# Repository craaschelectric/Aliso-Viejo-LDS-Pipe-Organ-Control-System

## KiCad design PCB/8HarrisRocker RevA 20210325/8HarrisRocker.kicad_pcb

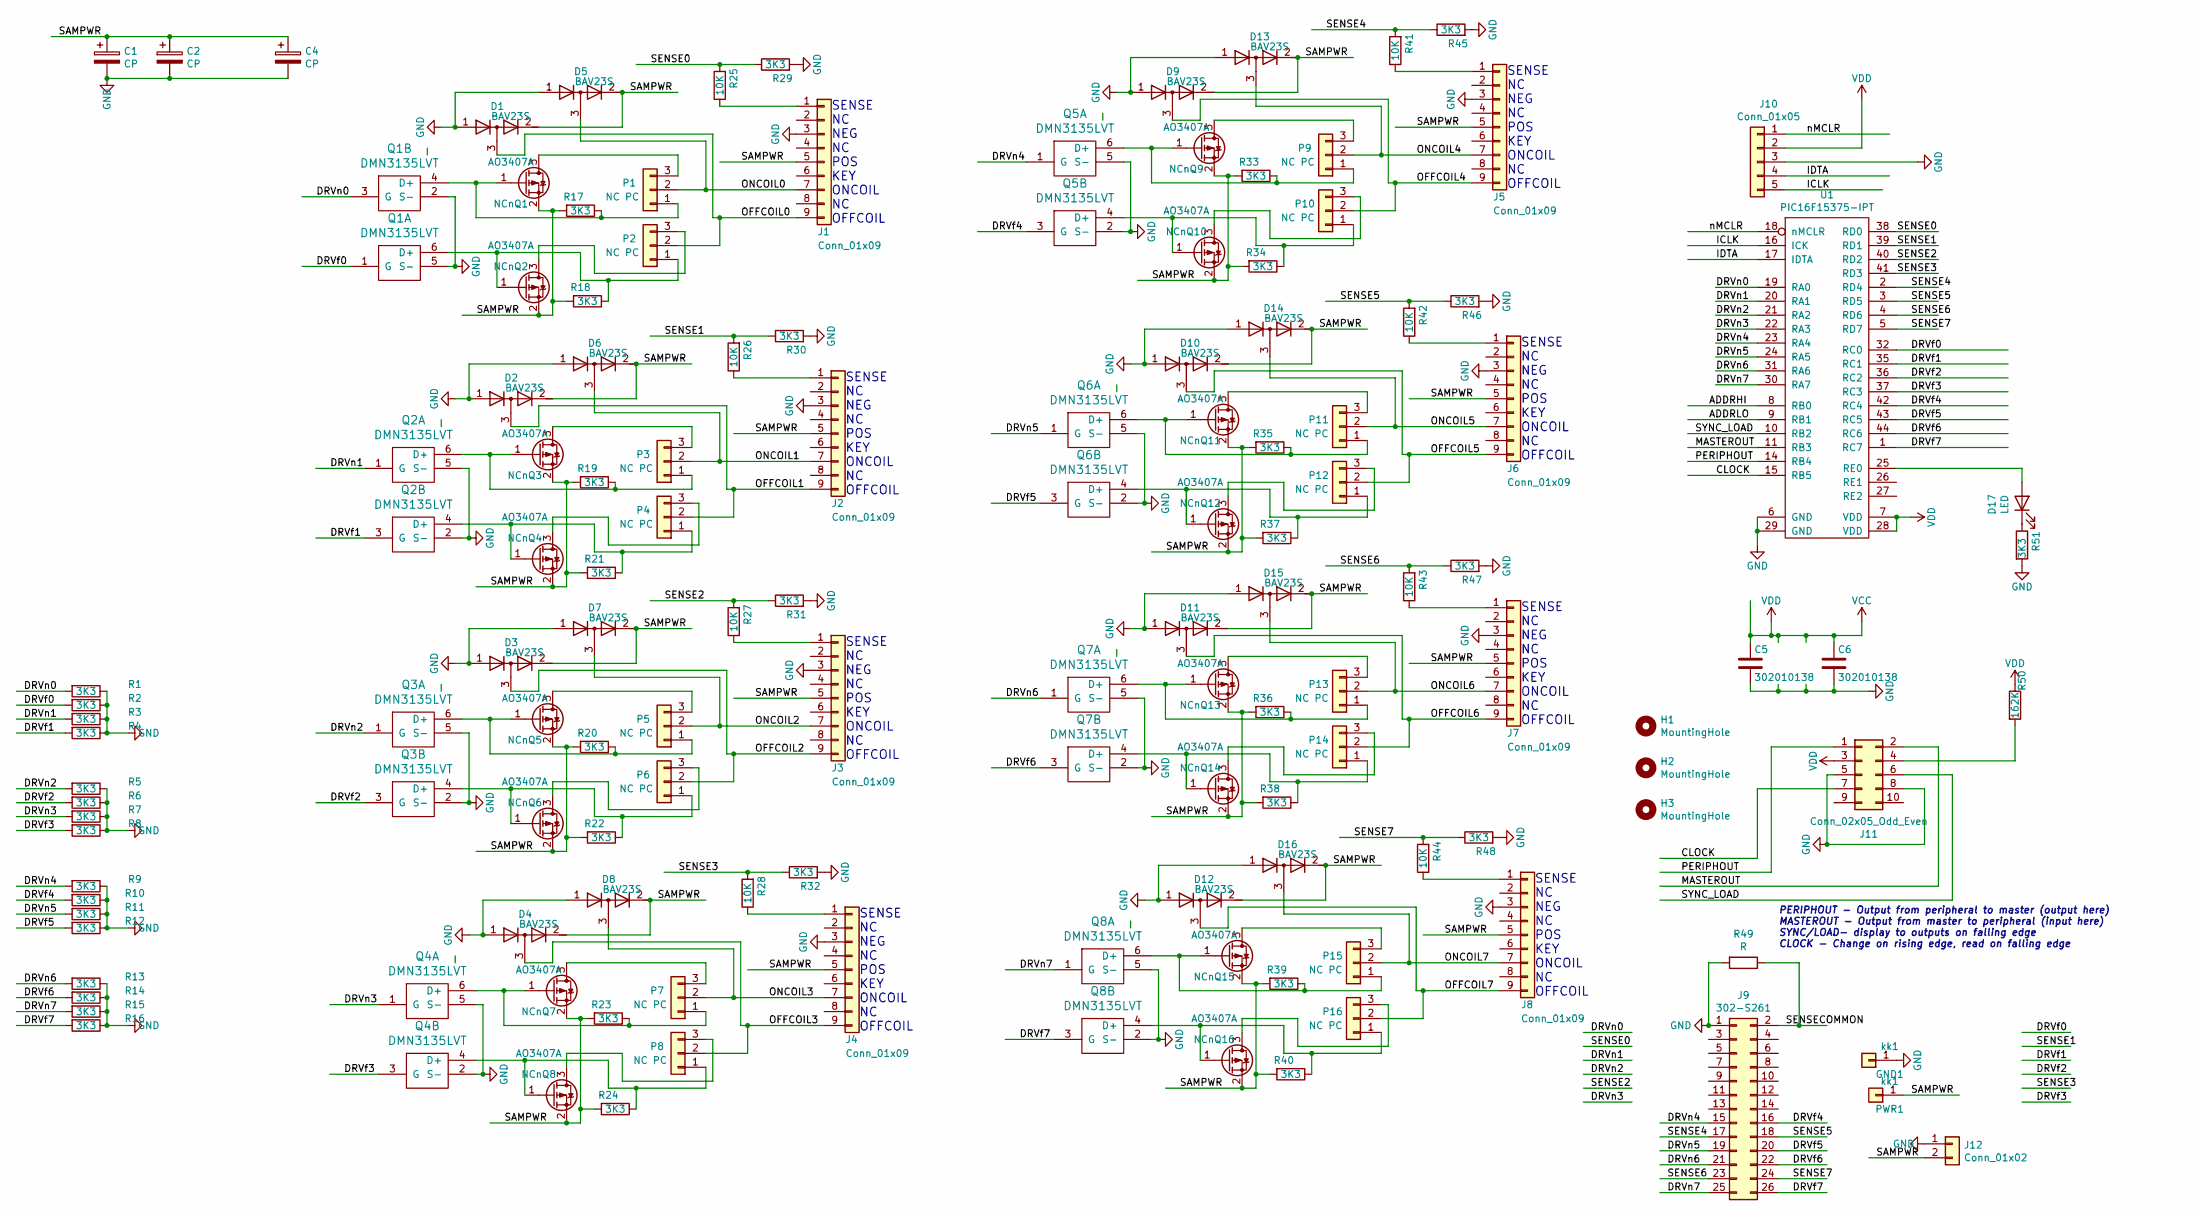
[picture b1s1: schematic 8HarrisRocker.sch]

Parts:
C1, C2, C4: CP; CP_Radial_D10.0mm_P2.50mm_P5.00mm
C5: 302010138; C_0805_2012Metric_Pad1.18x1.45mm_HandSolder
C6: 302010138; C_0603_1608Metric_Pad1.08x0.95mm_HandSolder
D1, D2, D3, D4, D5, D6, D7, D8, D9, D10, D11, D12, D13, D14, D15, D16: BAV23S; SOT-23_Handsoldering
D17: LED; LED_0805_2012Metric_Pad1.15x1.40mm_HandSolder
GND1: kk1; KK156-1
H1, H2, H3: MountingHole; MountingHole_3.2mm_M3
J1, J2, J3, J4, J5, J6, J7, J8: Conn_01x09; PinSocket_1x09_P2.54mm_Vertical
J9: 302-S261; 2x13_2.54mmShrouded
J10: Conn_01x05; PinHeader_1x05_P2.54mm_Vertical
J11: Conn_02x05_Odd_Even; RibbonCableSocket_10_OddEven
J12: Conn_01x02; TerminalBlock_Phoenix_PT-1,5-2-3.5-H_1x02_P3.50mm_Horizontal
NCnQ1, NCnQ2, NCnQ3, NCnQ4, NCnQ5, NCnQ6, NCnQ7, NCnQ8, NCnQ9, NCnQ10, NCnQ11, NCnQ12, NCnQ13, NCnQ14, NCnQ15, NCnQ16: AO3407A; SOT-23_Handsoldering
P1, P2, P3, P4, P5, P6, P7, P8, P9, P10, P11, P12, P13, P14, P15, P16: NC PC; 0603Jumper
PWR1: kk1; KK156-1
Q1, Q2, Q3, Q4, Q5, Q6, Q7, Q8: DMN3135LVT; SOT-23-6_Handsoldering
R1, R2, R3, R4, R5, R6, R7, R8, R9, R10, R11, R12, R13, R14, R15, R16, R17, R18, R19, R20, R21, R22, R23, R24, R29, R30, R31, R32, R33, R34, R35, R36, R37, R38, R39, R40, R45, R46, R47, R48, R51: 3K3; R_0603_1608Metric_Pad0.98x0.95mm_HandSolder
R25, R26, R27, R28, R41, R42, R43, R44: 10K; R_0603_1608Metric_Pad0.98x0.95mm_HandSolder
R49: R; R_0603_1608Metric_Pad0.98x0.95mm_HandSolder
R50: 162K; R_0603_1608Metric_Pad0.98x0.95mm_HandSolder
U1: PIC16F15375-IPT; LQFP-44_10x10mm_P0.8mm

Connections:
/CLOCK: J11.7, U1.15 (RB5)
/DRVf0: Q1.1 (G), R2.2, U1.32 (RC0)
/DRVf1: Q2.3 (G), R4.2, U1.35 (RC1)
/DRVf2: Q3.3 (G), R6.2, U1.36 (RC2)
/DRVf3: Q4.3 (G), R8.2, U1.37 (RC3)
/DRVf4: J9.16, Q5.3 (G), R10.2, U1.42 (RC4)
/DRVf5: J9.20, Q6.3 (G), R12.2, U1.43 (RC5)
/DRVf6: J9.22, Q7.3 (G), R14.2, U1.44 (RC6)
/DRVf7: J9.26, Q8.3 (G), R16.2, U1.1 (RC7)
/DRVn0: Q1.3 (G), R1.2, U1.19 (RA0)
/DRVn1: Q2.1 (G), R3.2, U1.20 (RA1)
/DRVn2: Q3.1 (G), R5.2, U1.21 (RA2)
/DRVn3: Q4.1 (G), R7.2, U1.22 (RA3)
/DRVn4: J9.15, Q5.1 (G), R9.2, U1.23 (RA4)
/DRVn5: J9.19, Q6.1 (G), R11.2, U1.24 (RA5)
/DRVn6: J9.21, Q7.1 (G), R13.2, U1.31 (RA6)
/DRVn7: J9.25, Q8.1 (G), R15.2, U1.30 (RA7)
/ICLK: J10.5, U1.16 (ICK)
/IDTA: J10.4, U1.17 (IDTA)
/MASTEROUT: J11.2, U1.11 (RB3)
/OFFCOIL0: D1.3 (common), J1.9, P2.2
/OFFCOIL1: D2.3 (common), J2.9, P4.2
/OFFCOIL2: D3.3 (common), J3.9, P6.2
/OFFCOIL3: D4.3 (common), J4.9, P8.2
/OFFCOIL4: D9.3 (common), J5.9, P10.2
/OFFCOIL5: D10.3 (common), J6.9, P12.2
/OFFCOIL6: D11.3 (common), J7.9, P14.2
/OFFCOIL7: D12.3 (common), J8.9, P16.2
/ONCOIL0: D5.3 (common), J1.7, P1.2
/ONCOIL1: D6.3 (common), J2.7, P3.2
/ONCOIL2: D7.3 (common), J3.7, P5.2
/ONCOIL3: D8.3 (common), J4.7, P7.2
/ONCOIL4: D13.3 (common), J5.7, P9.2
/ONCOIL5: D14.3 (common), J6.7, P11.2
/ONCOIL6: D15.3 (common), J7.7, P13.2
/ONCOIL7: D16.3 (common), J8.7, P15.2
/PERIPHOUT: J11.1, U1.14 (RB4)
/SAMPWR: C1.1, C2.1, C4.1, D1.2 (K), D2.2 (K), D3.2 (K), D4.2 (K), D5.2 (K), D6.2 (K), D7.2 (K), D8.2 (K), D9.2 (K), D10.2 (K), D11.2 (K), D12.2 (K), D13.2 (K), D14.2 (K), D15.2 (K), D16.2 (K), J1.5, J2.5, J3.5, J4.5, J5.5, J6.5, J7.5, J8.5, J12.2, NCnQ1.2 (S), NCnQ2.2 (S), NCnQ3.2 (S), NCnQ4.2 (S), NCnQ5.2 (S), NCnQ6.2 (S), NCnQ7.2 (S), NCnQ8.2 (S), NCnQ9.2 (S), NCnQ10.2 (S), NCnQ11.2 (S), NCnQ12.2 (S), NCnQ13.2 (S), NCnQ14.2 (S), NCnQ15.2 (S), NCnQ16.2 (S), PWR1.1, R17.2, R18.2, R19.2, R20.2, R21.2, R22.2, R23.2, R24.2, R33.2, R34.2, R35.2, R36.2, R37.2, R38.2, R39.2, R40.2
/SENSE0: R25.2, R29.1, U1.38 (RD0)
/SENSE1: R26.2, R30.1, U1.39 (RD1)
/SENSE2: R27.2, R31.1, U1.40 (RD2)
/SENSE3: R28.2, R32.1, U1.41 (RD3)
/SENSE4: J9.17, R41.2, R45.1, U1.2 (RD4)
/SENSE5: J9.18, R42.2, R46.1, U1.3 (RD5)
/SENSE6: J9.23, R43.2, R47.1, U1.4 (RD6)
/SENSE7: J9.24, R44.2, R48.1, U1.5 (RD7)
/SENSECOMMON: J9.2, R49.1
/SYNC_LOAD: J11.6, U1.10 (RB2)
/nMCLR: J10.1, U1.18 (nMCLR)
GND: C1.2, C2.2, C4.2, C5.2, C6.2, D1.1 (A), D2.1 (A), D3.1 (A), D4.1 (A), D5.1 (A), D6.1 (A), D7.1 (A), D8.1 (A), D9.1 (A), D10.1 (A), D11.1 (A), D12.1 (A), D13.1 (A), D14.1 (A), D15.1 (A), D16.1 (A), GND1.1, J1.3, J2.3, J3.3, J4.3, J5.3, J6.3, J7.3, J8.3, J9.1, J10.3, J11.5, J11.8, J12.1, Q1.2 (S-), Q1.5 (S-), Q2.2 (S-), Q2.5 (S-), Q3.2 (S-), Q3.5 (S-), Q4.2 (S-), Q4.5 (S-), Q5.2 (S-), Q5.5 (S-), Q6.2 (S-), Q6.5 (S-), Q7.2 (S-), Q7.5 (S-), Q8.2 (S-), Q8.5 (S-), R1.1, R2.1, R3.1, R4.1, R5.1, R6.1, R7.1, R8.1, R9.1, R10.1, R11.1, R12.1, R13.1, R14.1, R15.1, R16.1, R29.2, R30.2, R31.2, R32.2, R45.2, R46.2, R47.2, R48.2, R49.2, R51.2, U1.6 (GND), U1.29 (GND)
unnamed: D17.1 (K), R51.1
unnamed: D17.2 (A), U1.25 (RE0)
unnamed: J1.1, R25.1
unnamed: J2.1, R26.1
unnamed: J3.1, R27.1
unnamed: J4.1, R28.1
unnamed: J5.1, R41.1
unnamed: J6.1, R42.1
unnamed: J7.1, R43.1
unnamed: J8.1, R44.1
unnamed: J11.4, R50.2
unnamed: NCnQ1.1 (G), P1.1, Q1.4 (D+), R17.1
unnamed: NCnQ1.3 (D), P1.3
unnamed: NCnQ2.1 (G), P2.1, Q1.6 (D+), R18.1
unnamed: NCnQ2.3 (D), P2.3
unnamed: NCnQ3.1 (G), P3.1, Q2.6 (D+), R19.1
unnamed: NCnQ3.3 (D), P3.3
unnamed: NCnQ4.1 (G), P4.1, Q2.4 (D+), R21.1
unnamed: NCnQ4.3 (D), P4.3
unnamed: NCnQ5.1 (G), P5.1, Q3.6 (D+), R20.1
unnamed: NCnQ5.3 (D), P5.3
unnamed: NCnQ6.1 (G), P6.1, Q3.4 (D+), R22.1
unnamed: NCnQ6.3 (D), P6.3
unnamed: NCnQ7.1 (G), P7.1, Q4.6 (D+), R23.1
unnamed: NCnQ7.3 (D), P7.3
unnamed: NCnQ8.1 (G), P8.1, Q4.4 (D+), R24.1
unnamed: NCnQ8.3 (D), P8.3
unnamed: NCnQ9.1 (G), P9.1, Q5.6 (D+), R33.1
unnamed: NCnQ9.3 (D), P9.3
unnamed: NCnQ10.1 (G), P10.1, Q5.4 (D+), R34.1
unnamed: NCnQ10.3 (D), P10.3
unnamed: NCnQ11.1 (G), P11.1, Q6.6 (D+), R35.1
unnamed: NCnQ11.3 (D), P11.3
unnamed: NCnQ12.1 (G), P12.1, Q6.4 (D+), R37.1
unnamed: NCnQ12.3 (D), P12.3
unnamed: NCnQ13.1 (G), P13.1, Q7.6 (D+), R36.1
unnamed: NCnQ13.3 (D), P13.3
unnamed: NCnQ14.1 (G), P14.1, Q7.4 (D+), R38.1
unnamed: NCnQ14.3 (D), P14.3
unnamed: NCnQ15.1 (G), P15.1, Q8.6 (D+), R39.1
unnamed: NCnQ15.3 (D), P15.3
unnamed: NCnQ16.1 (G), P16.1, Q8.4 (D+), R40.1
unnamed: NCnQ16.3 (D), P16.3
VCC: C5.1, C6.1, J10.2, J11.3, R50.1, U1.7 (VDD), U1.28 (VDD)

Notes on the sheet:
SENSE NC NEG NC POS KEY ONCOIL NC OFFCOIL
PERIPHOUT - Output from peripheral to master (output here) MASTEROUT - Output from master to peripheral (input here) SYNC/LOAD- display to outputs on falling edge CLOCK - Change on rising edge, read on falling edge

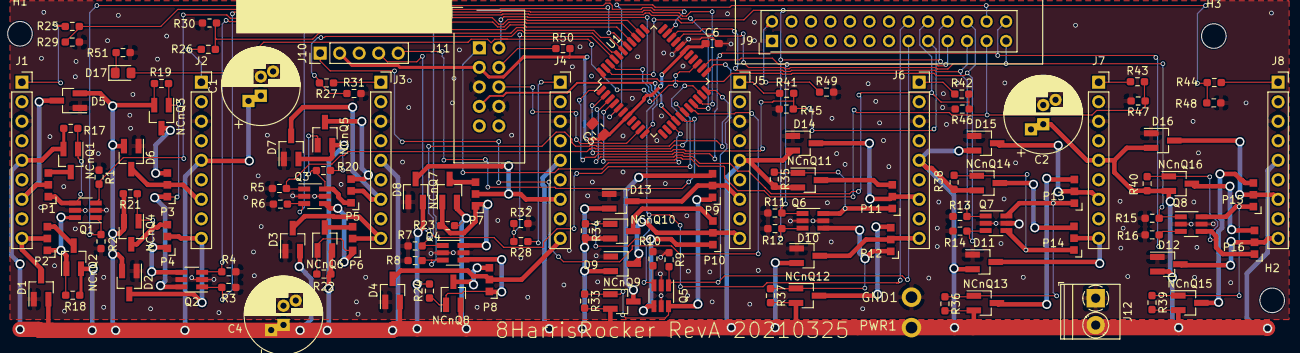
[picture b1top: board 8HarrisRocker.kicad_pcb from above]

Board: 2 copper layers, 131 parts (0 on the bottom side), 94 nets.

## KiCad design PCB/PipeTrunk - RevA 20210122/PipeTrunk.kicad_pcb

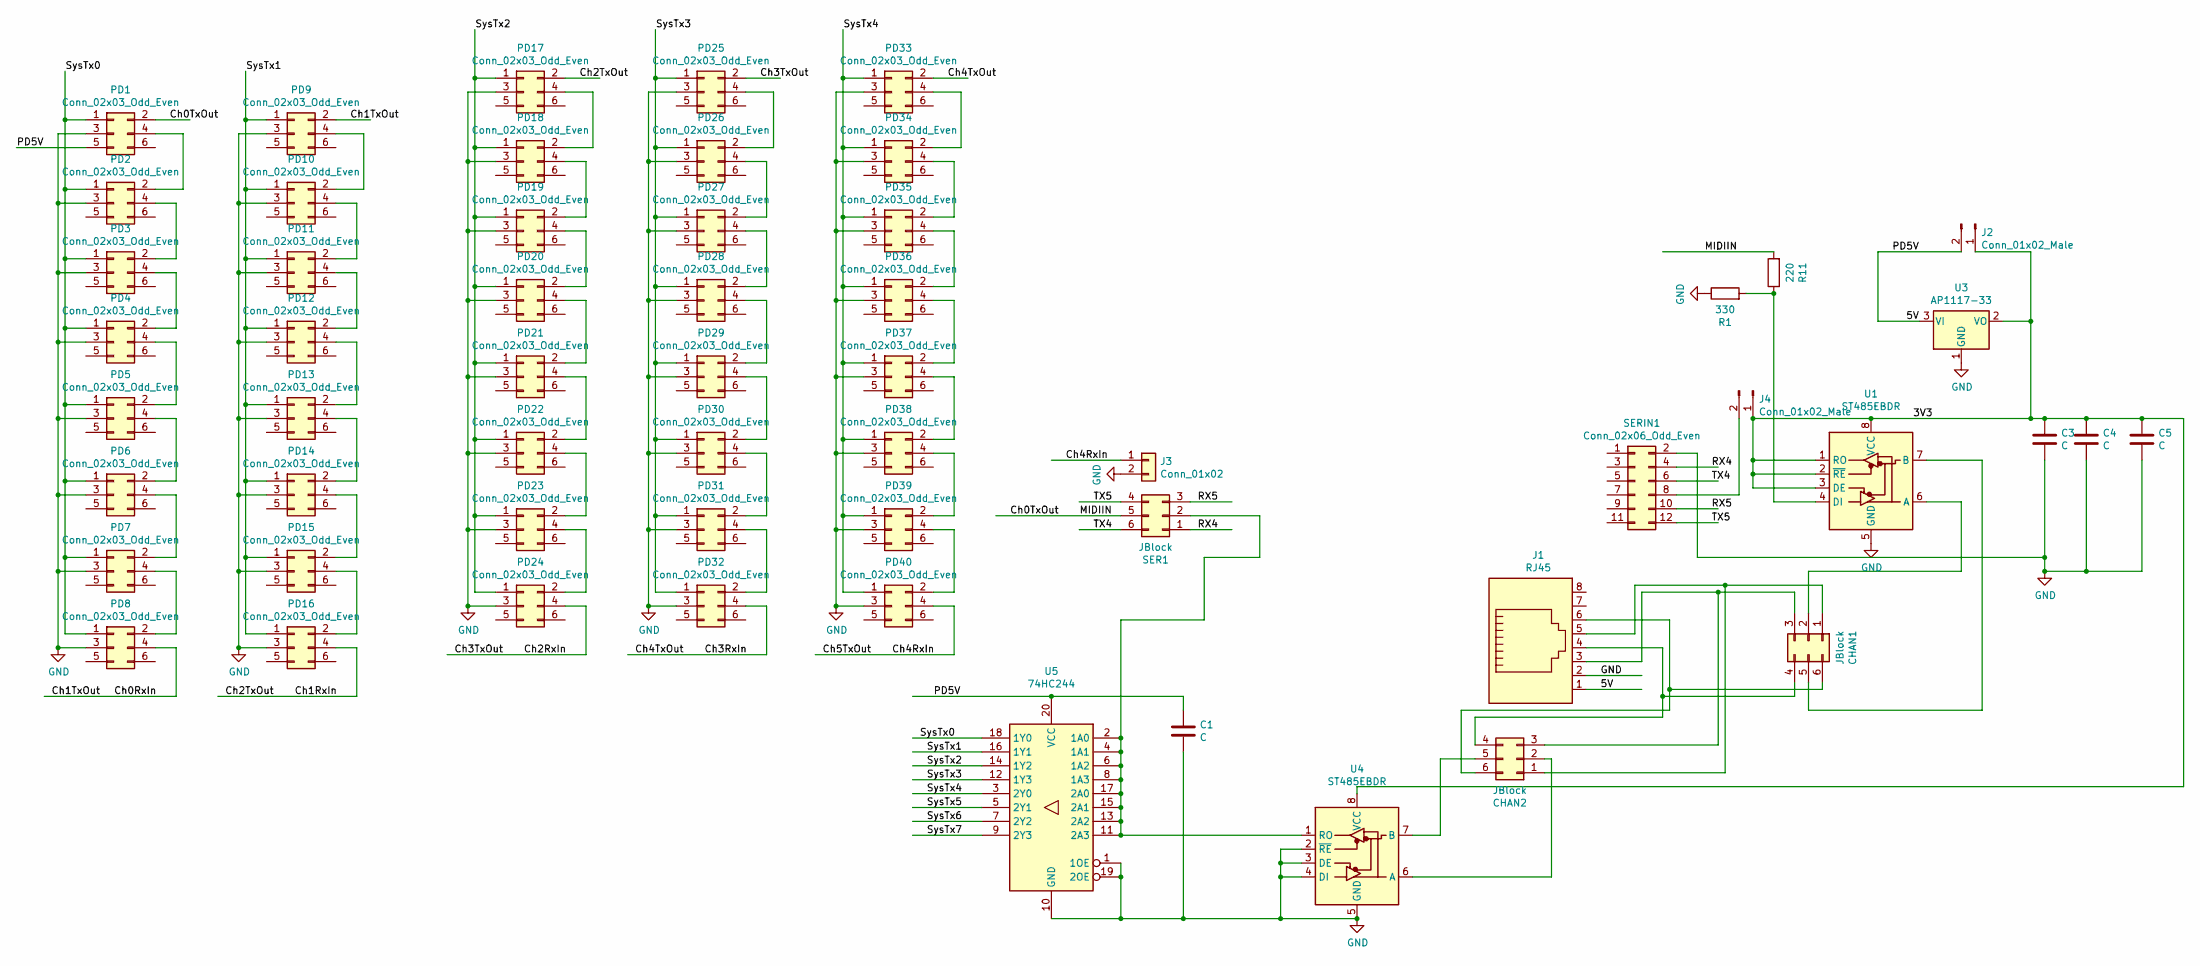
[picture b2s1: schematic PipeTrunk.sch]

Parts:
C1, C3: C; C_0603_1608Metric_Pad1.08x0.95mm_HandSolder
C4, C5: C; C_0805_2012Metric_Pad1.15x1.40mm_HandSolder
CHAN1, CHAN2: JBlock; H2X3-2.54
J1: RJ45; RJ45_Amphenol_54602-x08_Horizontal
J2, J4: Conn_01x02_Male; H2-2.54
J3: Conn_01x02; H2-2.54
PD1, PD2, PD3, PD4, PD5, PD6, PD7, PD8, PD9, PD10, PD11, PD12, PD13, PD14, PD15, PD16, PD17, PD18, PD19, PD20, PD21, PD22, PD23, PD24, PD25, PD26, PD27, PD28, PD29, PD30, PD31, PD32, PD33, PD34, PD35, PD36, PD37, PD38, PD39, PD40: Conn_02x03_Odd_Even; RibbonCableSocket_6_OddEven
R1: 330; R_0603_1608Metric_Pad0.98x0.95mm_HandSolder
R11: 220; R_0603_1608Metric_Pad0.98x0.95mm_HandSolder
SER1: JBlock; H2X3-2.54
SERIN1: Conn_02x06_Odd_Even; RibbonCableSocket_12_OddEven
U1, U4: ST485EBDR; SOIC-8_3.9x4.9mm_P1.27mm
U3: AP1117-33; SOT-223-3_TabPin2
U5: 74HC244; SOIC-20W_7.5x12.8mm_P1.27mm

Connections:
/3V3: C3.1, C4.1, C5.1, J2.1, J4.1, U1.1 (RO), U1.2 (~RE), U1.3 (DE), U1.8 (VCC), U3.2 (VO), U4.8 (VCC)
/5V: C1.1, J1.1, J2.2, PD1.5, U3.3 (VI), U5.20 (VCC)
/Ch0RxIn: PD8.4, PD9.2
/Ch0TxOut: PD1.2, R11.2, SER1.5
/Ch1RxIn: PD16.4, PD17.2
/Ch2RxIn: PD24.4, PD25.2
/Ch3RxIn: PD32.4, PD33.2
/Ch4RxIn: J3.1, PD40.4
/RX4: SER1.1, SERIN1.4
/RX5: SER1.3, SERIN1.10
/SysTx0: PD1.1, PD2.1, PD3.1, PD4.1, PD5.1, PD6.1, PD7.1, PD8.1, U5.18 (1Y0)
/SysTx1: PD9.1, PD10.1, PD11.1, PD12.1, PD13.1, PD14.1, PD15.1, PD16.1, U5.16 (1Y1)
/SysTx2: PD17.1, PD18.1, PD19.1, PD20.1, PD21.1, PD22.1, PD23.1, PD24.1, U5.14 (1Y2)
/SysTx3: PD25.1, PD26.1, PD27.1, PD28.1, PD29.1, PD30.1, PD31.1, PD32.1, U5.12 (1Y3)
/SysTx4: PD33.1, PD34.1, PD35.1, PD36.1, PD37.1, PD38.1, PD39.1, PD40.1, U5.3 (2Y0)
/TX4: SER1.6, SERIN1.6
/TX5: SER1.4, SERIN1.12
GND: C1.2, C3.2, C4.2, C5.2, J1.2, J3.2, PD1.3, PD2.3, PD3.3, PD4.3, PD5.3, PD6.3, PD7.3, PD8.3, PD9.3, PD10.3, PD11.3, PD12.3, PD13.3, PD14.3, PD15.3, PD16.3, PD17.3, PD18.3, PD19.3, PD20.3, PD21.3, PD22.3, PD23.3, PD24.3, PD25.3, PD26.3, PD27.3, PD28.3, PD29.3, PD30.3, PD31.3, PD32.3, PD33.3, PD34.3, PD35.3, PD36.3, PD37.3, PD38.3, PD39.3, PD40.3, R1.1, SERIN1.2, U1.5 (GND), U3.1 (GND), U4.2 (~RE), U4.3 (DE), U4.4 (DI), U4.5 (GND), U5.1 (1OE), U5.10 (GND), U5.19 (2OE)
unnamed: CHAN1.1, CHAN2.1, J1.5
unnamed: CHAN1.2, U1.6 (A)
unnamed: CHAN1.3, CHAN2.3, J1.3
unnamed: CHAN1.4, CHAN2.4, J1.4
unnamed: CHAN1.5, U1.7 (B)
unnamed: CHAN1.6, CHAN2.6, J1.6
unnamed: CHAN2.2, U4.6 (A)
unnamed: CHAN2.5, U4.7 (B)
unnamed: J4.2, SERIN1.8
unnamed: PD1.4, PD2.2
unnamed: PD2.4, PD3.2
unnamed: PD3.4, PD4.2
unnamed: PD4.4, PD5.2
unnamed: PD5.4, PD6.2
unnamed: PD6.4, PD7.2
unnamed: PD7.4, PD8.2
unnamed: PD9.4, PD10.2
unnamed: PD10.4, PD11.2
unnamed: PD11.4, PD12.2
unnamed: PD12.4, PD13.2
unnamed: PD13.4, PD14.2
unnamed: PD14.4, PD15.2
unnamed: PD15.4, PD16.2
unnamed: PD17.4, PD18.2
unnamed: PD18.4, PD19.2
unnamed: PD19.4, PD20.2
unnamed: PD20.4, PD21.2
unnamed: PD21.4, PD22.2
unnamed: PD22.4, PD23.2
unnamed: PD23.4, PD24.2
unnamed: PD25.4, PD26.2
unnamed: PD26.4, PD27.2
unnamed: PD27.4, PD28.2
unnamed: PD28.4, PD29.2
unnamed: PD29.4, PD30.2
unnamed: PD30.4, PD31.2
unnamed: PD31.4, PD32.2
unnamed: PD33.4, PD34.2
unnamed: PD34.4, PD35.2
unnamed: PD35.4, PD36.2
unnamed: PD36.4, PD37.2
unnamed: PD37.4, PD38.2
unnamed: PD38.4, PD39.2
unnamed: PD39.4, PD40.2
unnamed: R1.2, R11.1, U1.4 (DI)
unnamed: SER1.2, U4.1 (RO), U5.2 (1A0), U5.4 (1A1), U5.6 (1A2), U5.8 (1A3), U5.11 (2A3), U5.13 (2A2), U5.15 (2A1), U5.17 (2A0)

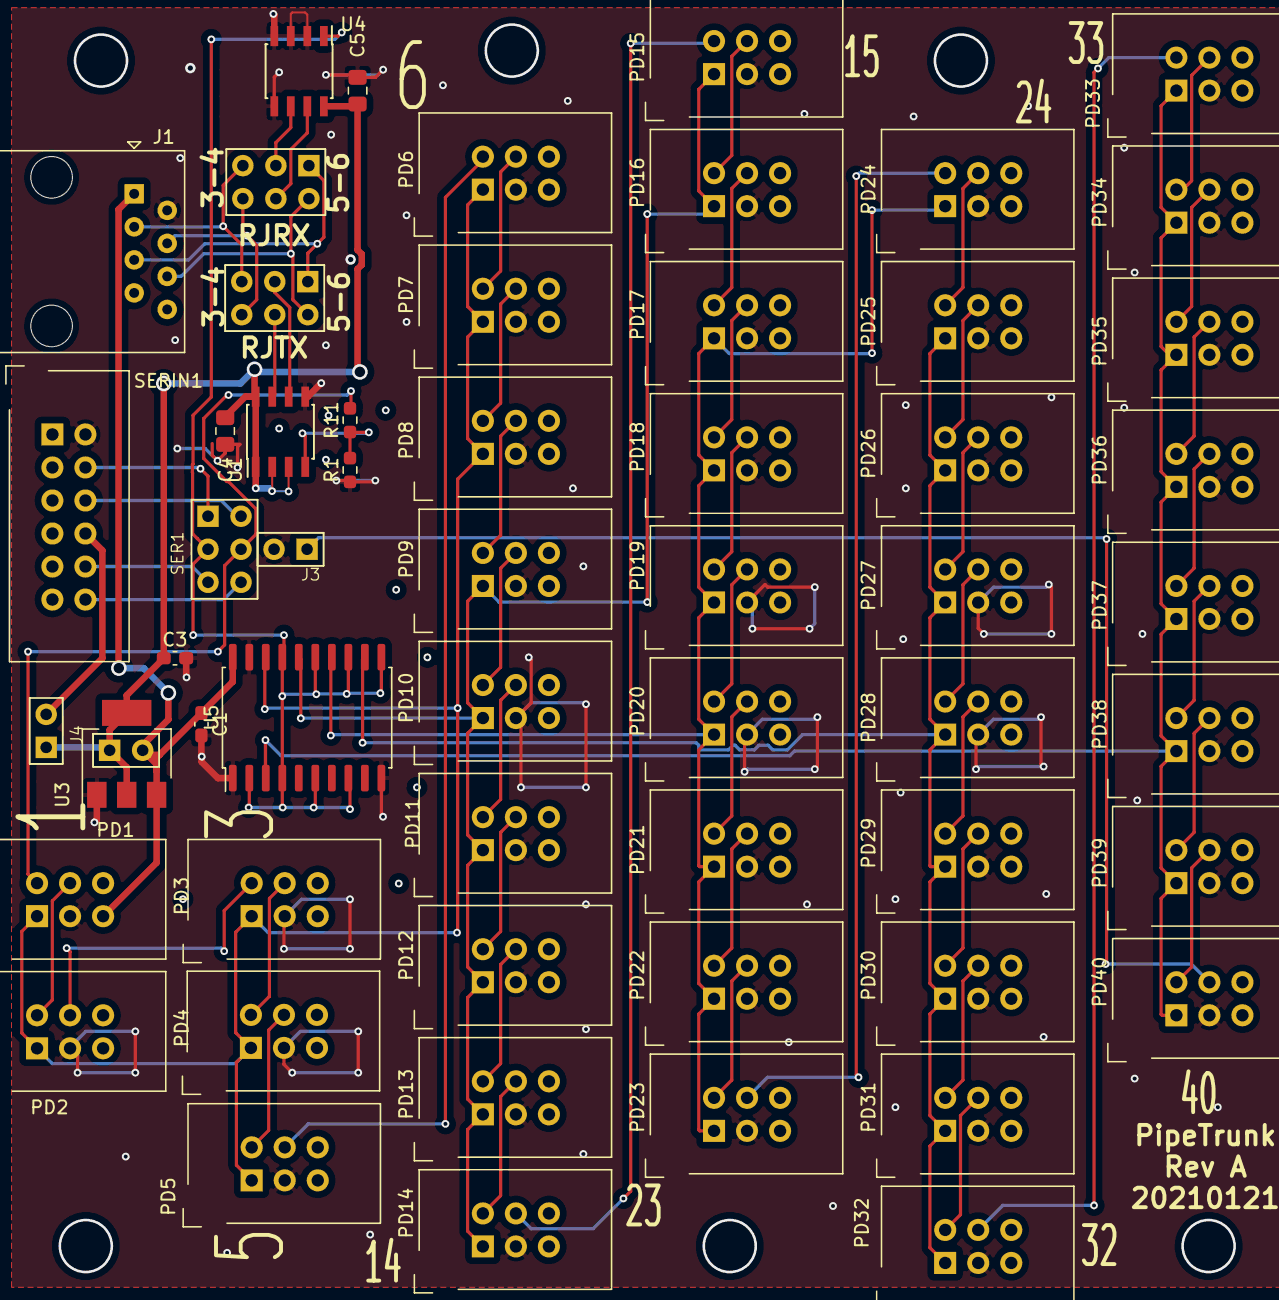
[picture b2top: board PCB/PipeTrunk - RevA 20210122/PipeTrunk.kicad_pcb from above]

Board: 2 copper layers, 58 parts (0 on the bottom side), 64 nets.

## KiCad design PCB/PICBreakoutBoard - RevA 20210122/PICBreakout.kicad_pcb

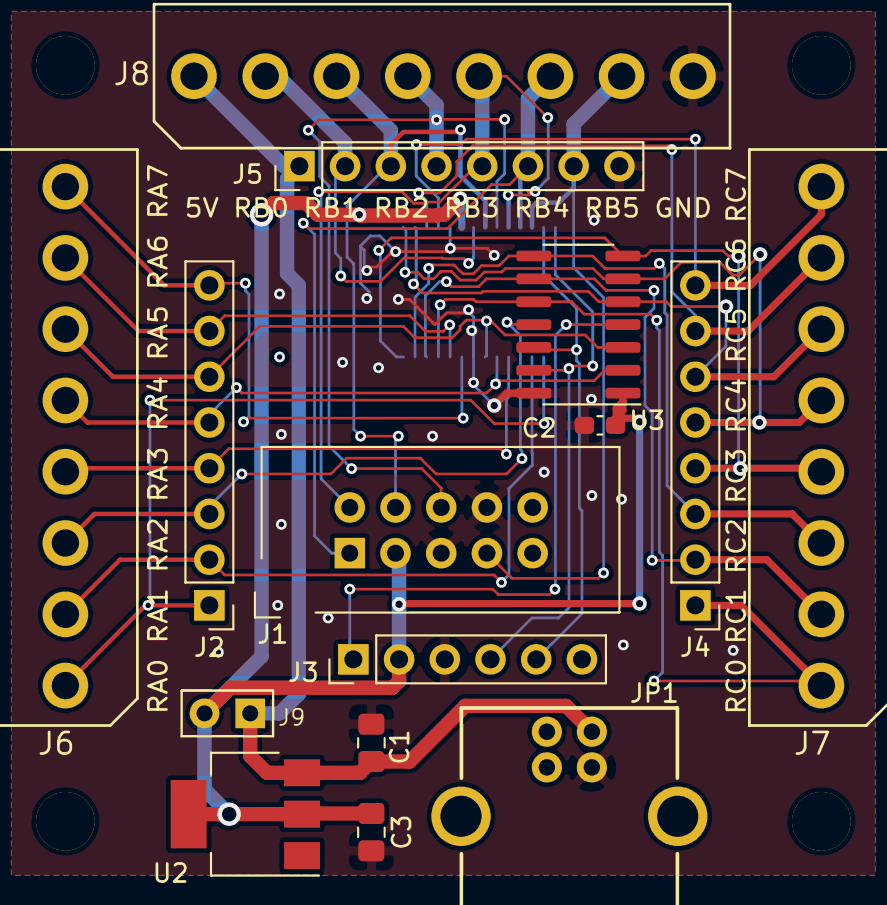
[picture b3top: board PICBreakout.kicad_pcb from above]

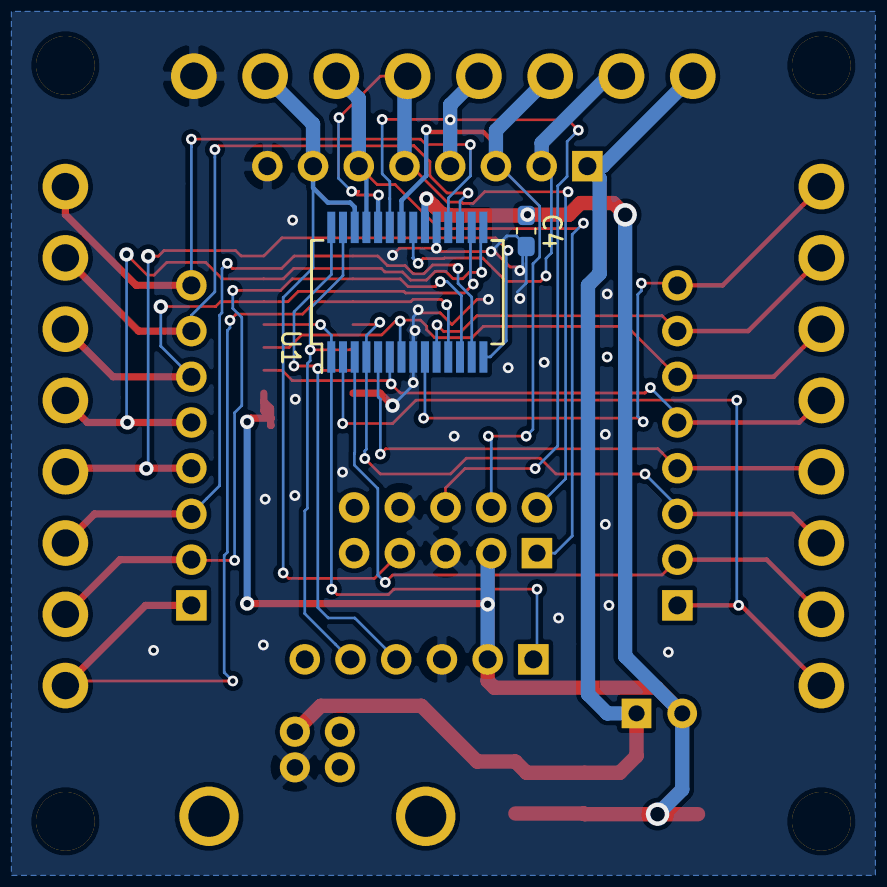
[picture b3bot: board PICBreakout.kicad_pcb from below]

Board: 2 copper layers, 21 parts (2 on the bottom side), 28 nets.

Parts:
C1, C3: 302010138; C_0805_2012Metric_Pad1.18x1.45mm_HandSolder
C2, C4: 302010138; C_0603_1608Metric_Pad1.08x0.95mm_HandSolder
J1: Conn_02x05_Odd_Even; RibbonCableSocket_10_OddEven
J2, J4, J5: Conn_01x08; PinHeader_1x08_P2.54mm_Vertical
J3: Conn_01x05; PinHeader_1x06_P2.54mm_Vertical
J6, J7, J8: Conn_01x08; KK156-8
J9: Conn_01x02; H2-2.54
JP1: DIP-USB-B-TYPE-FMAL_4+2P-2.0-90D_; USB4+2-2.5-90D-15.8X12MM
M1, M2, M3, M4: Conn_01x01; Mounting#4
U1: PIC18F26Q10-SS; SSOP-28_5.3x10.2mm_P0.65mm
U2: LM1117-3.3; SOT-223-3_TabPin2
U3: PIC16F1525; SO-14_3.9x8.65mm_P1.27mm

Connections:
/5V: C1.1, J5.1, J8.1, J9.1, JP1.VBUS, U2.3
/CLK: J1.7, J5.7, J8.7, U1.26
/MSTOUT: J1.2, J5.5, J8.5, U1.24
/PEROUT: J1.1, J5.6, J8.6, U1.25
/RA0: J2.1, J6.1, U1.2
/RA1: J2.2, J6.2, U1.3
/RA2: J2.3, J6.3, U1.4, U3.11
/RA3: J2.4, J6.4, U1.5
/RA4: J2.5, J6.5, U1.6, U3.2
/RA5: J2.6, J6.6, U1.7, U3.3
/RA6: J2.7, J6.7, U1.10
/RA7: J2.8, J6.8, U1.9
/RB0: J5.2, J8.2, U1.21
/RC0: J4.1, J7.1, U1.11, U3.10
/RC1: J4.2, J7.2, U1.12, U3.9
/RC2: J4.3, J7.3, U1.13, U3.8
/RC3: J4.4, J7.4, U1.14, U3.7
/RC4: J4.5, J7.5, U1.15, U3.6
/RC5: J4.6, J7.6, U1.16, U3.5
/RC6: J4.7, J7.7, U1.17
/RC7: J4.8, J7.8, U1.18
/SYNC: J1.6, J5.4, J8.4, U1.23
/nRST: J1.4, J5.3, J8.3, U1.22
GND: C1.2, C2.2, C3.2, C4.2, J1.5, J1.8, J3.3, J5.8, J8.8, JP1.GND, U1.8, U1.19, U3.14
unnamed: J3.1, U1.1, U3.4
unnamed: J3.4, U1.28, U3.13
unnamed: J3.5, U1.27, U3.12
VDD: C2.1, C3.1, C4.1, J1.3, J3.2, J9.2, U1.20, U2.2, U3.1

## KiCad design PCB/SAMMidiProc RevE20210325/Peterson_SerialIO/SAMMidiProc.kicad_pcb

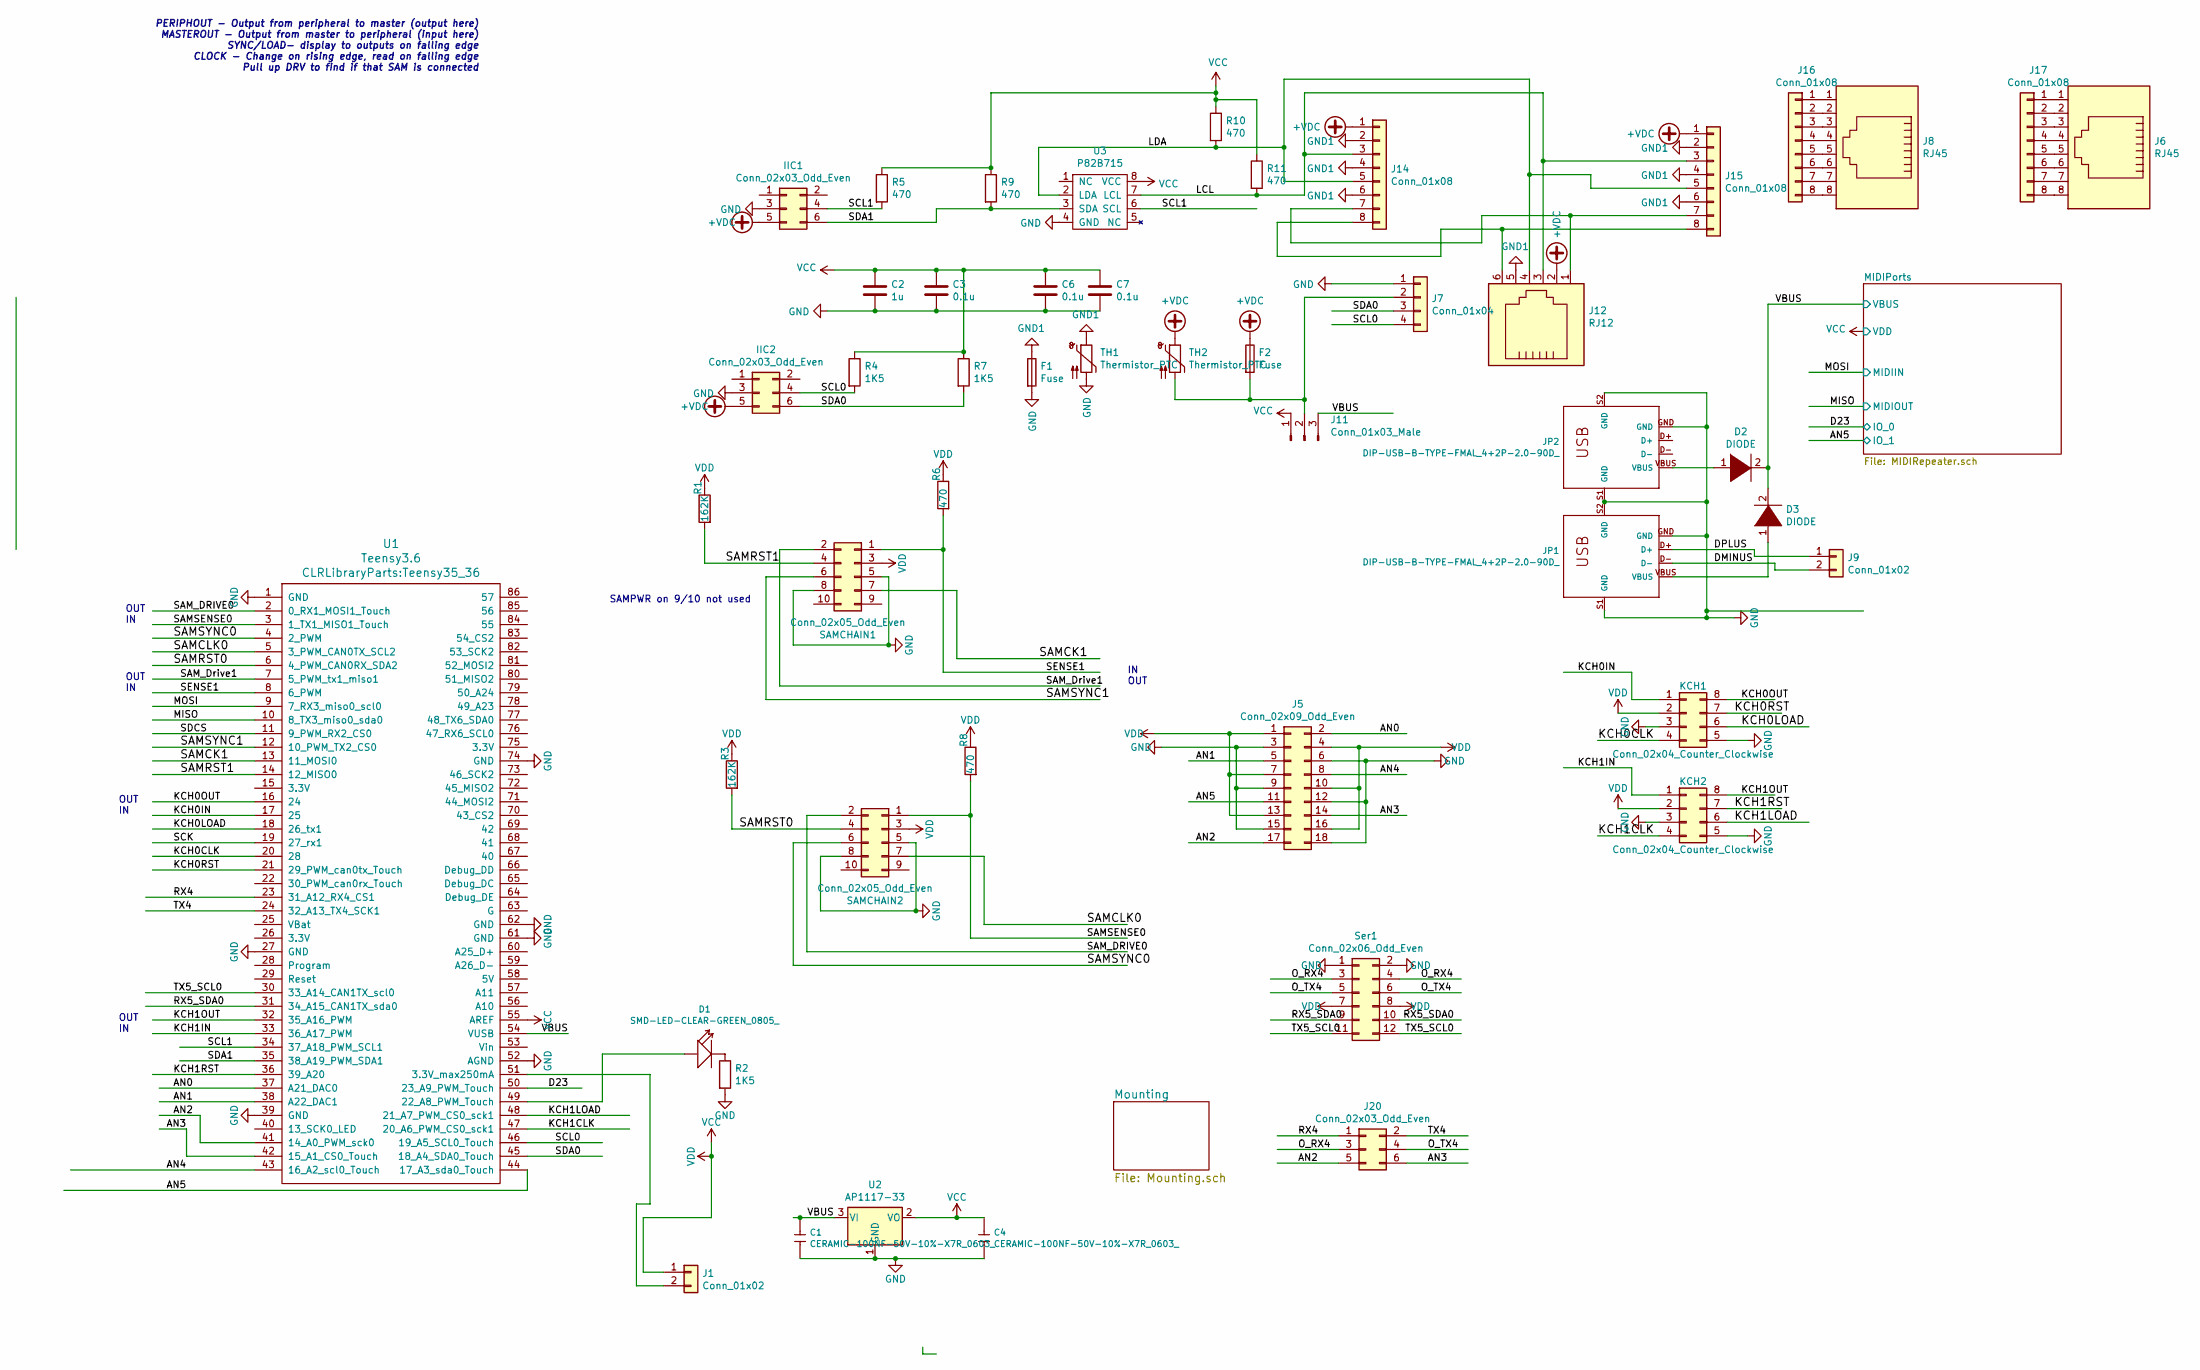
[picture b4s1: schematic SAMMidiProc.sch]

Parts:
C1: CERAMIC-100NF-50V-10%-X7R_0603_; C0805; MPN CC0603KRX7R9BB104
C2: 1u; C_0805_2012Metric_Pad1.18x1.45mm_HandSolder
C3, C6, C7: 0.1u; C_0603_1608Metric_Pad1.08x0.95mm_HandSolder
C4: CERAMIC-100NF-50V-10%-X7R_0603_; C_0603_1608Metric_Pad1.08x0.95mm_HandSolder; MPN CC0603KRX7R9BB104
D1: SMD-LED-CLEAR-GREEN_0805_; LED-0805; MPN 17-215SYGC_S530-E2_TR8
D2, D3: DIODE; D_SMA_Handsoldering_APin1
F1, F2: Fuse; Fuseholder_Blade_Mini_Keystone_3568
IIC1, IIC2: Conn_02x03_Odd_Even; RibbonCableSocket_6_OddEven
J1, J9: Conn_01x02; PinHeader_1x02_P2.54mm_Vertical
J5: Conn_02x09_Odd_Even; RibbonCableSocket_18_OddEven
J6, J8: RJ45; RJ45_Amphenol_54602-x08_Horizontal
J7: Conn_01x04; PinHeader_1x04_P2.54mm_Vertical
J11: Conn_01x03_Male; PinHeader_1x03_P2.54mm_Vertical
J12: RJ12; RJ12_Amphenol_54601
J14, J15, J16, J17: Conn_01x08; PinHeader_1x08_P2.54mm_Vertical
J20: Conn_02x03_Odd_Even; PinHeader_2x03_P2.54mm_Vertical
JP1, JP2: DIP-USB-B-TYPE-FMAL_4+2P-2.0-90D_; USB4+2-2.5-90D-15.8X12MM
KCH1, KCH2: Conn_02x04_Counter_Clockwise; RibbonCableSocket_8_CCW
R1, R3: 162K; R_0603_1608Metric_Pad0.98x0.95mm_HandSolder
R2, R4, R7: 1K5; R_0603_1608Metric_Pad0.98x0.95mm_HandSolder
R5, R6, R8, R9, R10, R11: 470; R_0603_1608Metric_Pad0.98x0.95mm_HandSolder
SAMCHAIN1, SAMCHAIN2: Conn_02x05_Odd_Even; RibbonCableSocket_10_OddEven
Ser1: Conn_02x06_Odd_Even; RibbonCableSocket_12_OddEven
TH1, TH2: Thermistor_PTC; R_2512_6332Metric
U1: Teensy3.6; Teensy35_36
U2: AP1117-33; SOT-223-3_TabPin2
U3: P82B715; SOIC-8_3.9x4.9mm_P1.27mm

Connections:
+VDC: F2.1, IIC1.5, IIC2.5, J12.2, J14.1, J15.1, TH2.1
/AN0: J5.2, U1.37 (A21_DAC0)
/AN1: J5.5, U1.38 (A22_DAC1)
/AN2: J5.17, J20.5, U1.41 (14_A0_PWM_sck0)
/AN3: J5.14, J20.6, U1.42 (15_A1_CS0_Touch)
/AN4: J5.8, U1.43 (16_A2_scl0_Touch)
/AN5: J5.11, U1.44 (17_A3_sda0_Touch); also elsewhere on the board
/D23: U1.50 (23_A9_PWM_Touch); also elsewhere on the board
/DMINUS: J9.2, JP1.D-
/DPLUS: J9.1, JP1.D+
/KCH0CLK: KCH1.4, U1.20 (28)
/KCH0IN: KCH1.1, U1.17 (25)
/KCH0LOAD: KCH1.6, U1.18 (26_tx1)
/KCH0OUT: KCH1.8, U1.16 (24)
/KCH0RST: KCH1.7, U1.21 (29_PWM_can0tx_Touch)
/KCH1CLK: KCH2.4, U1.47 (20_A6_PWM_CS0_sck1)
/KCH1IN: KCH2.1, U1.33 (36_A17_PWM)
/KCH1LOAD: KCH2.6, U1.48 (21_A7_PWM_CS0_sck1)
/KCH1OUT: KCH2.8, U1.32 (35_A16_PWM)
/KCH1RST: KCH2.7, U1.36 (39_A20)
/LCL: J12.3, J14.3, J15.3, R11.2, U3.7 (LCL)
/LDA: J12.4, J14.5, J15.5, R10.2, U3.2 (LDA)
/MISO: U1.10 (8_TX3_miso0_sda0); also elsewhere on the board
/MOSI: U1.9 (7_RX3_miso0_scl0); also elsewhere on the board
/O_RX4: J20.3, Ser1.3, Ser1.4
/O_TX4: J20.4, Ser1.5, Ser1.6
/RX4: J20.1, U1.23 (31_A12_RX4_CS1)
/RX5_SDA0: Ser1.9, Ser1.10, U1.31 (34_A15_CAN1TX_sda0)
/SAMCK1: SAMCHAIN1.7, U1.13 (11_MOSI0)
/SAMCLK0: SAMCHAIN2.7, U1.5 (3_PWM_CAN0TX_SCL2)
/SAMRST0: R3.2, SAMCHAIN2.4, U1.6 (4_PWM_CAN0RX_SDA2)
/SAMRST1: R1.2, SAMCHAIN1.4, U1.14 (12_MISO0)
/SAMSENSE0: R8.2, SAMCHAIN2.1, U1.3 (1_TX1_MISO1_Touch)
/SAMSYNC0: SAMCHAIN2.6, U1.4 (2_PWM)
/SAMSYNC1: SAMCHAIN1.6, U1.12 (10_PWM_TX2_CS0)
/SAM_DRIVE0: SAMCHAIN2.2, U1.2 (0_RX1_MOSI1_Touch)
/SAM_Drive1: SAMCHAIN1.2, U1.7 (5_PWM_tx1_miso1)
/SCL0: IIC2.4, J7.4, R4.2, U1.46 (19_A5_SCL0_Touch)
/SCL1: IIC1.4, R5.2, U1.34 (37_A18_PWM_SCL1), U3.6 (SCL)
/SDA0: IIC2.6, J7.3, R7.2, U1.45 (18_A4_SDA0_Touch)
/SDA1: IIC1.6, R9.2, U1.35 (38_A19_PWM_SDA1), U3.3 (SDA)
/SENSE1: R6.2, SAMCHAIN1.1, U1.8 (6_PWM)
/TX4: J20.2, U1.24 (32_A13_TX4_SCK1)
/TX5_SCL0: Ser1.11, Ser1.12, U1.30 (33_A14_CAN1TX_scl0)
/VBUS: C1.1, D2.2 (A), D3.2 (A), J11.3, U1.54 (VUSB), U2.3 (VI); also elsewhere on the board
GND: C1.2, C2.2, C3.2, C4.2, C6.2, C7.2, F1.2, IIC1.3, IIC2.3, J5.3, J5.6, J5.9, J5.12, J5.15, J5.18, J7.1, JP1.GND, JP1.S1 (GND), JP1.S2 (GND), JP2.GND, JP2.S1 (GND), JP2.S2 (GND), KCH1.3, KCH1.5, KCH2.3, KCH2.5, R2.2, SAMCHAIN1.5, SAMCHAIN1.8, SAMCHAIN2.5, SAMCHAIN2.8, Ser1.1, Ser1.2, TH1.2, U1.1 (GND), U1.27 (GND), U1.39 (GND), U1.52 (AGND), U1.61 (GND), U1.62 (GND), U1.74 (GND), U2.1 (GND), U3.4 (GND); also elsewhere on the board
GND1: F1.1, J12.5, J14.2, J14.4, J14.6, J15.2, J15.4, J15.6, TH1.1
unnamed: D1.1 (+), U1.49 (22_A8_PWM_Touch)
unnamed: D1.2 (-), R2.1
unnamed: D2.1 (K), JP2.VBUS
unnamed: D3.1 (K), JP1.VBUS
unnamed: F2.2, J7.2, J11.2, TH2.2
unnamed: J1.2, U1.51 (3.3V_max250mA)
unnamed: J12.1, J14.7, J15.7
unnamed: J12.6, J14.8, J15.8
unnamed: J8.1, J16.1
unnamed: J8.2, J16.2
unnamed: J8.3, J16.3
unnamed: J8.4, J16.4
unnamed: J8.5, J16.5
unnamed: J8.6, J16.6
unnamed: J8.7, J16.7
unnamed: J8.8, J16.8
unnamed: J6.1, J17.1
unnamed: J6.2, J17.2
unnamed: J6.3, J17.3
unnamed: J6.4, J17.4
unnamed: J6.5, J17.5
unnamed: J6.6, J17.6
unnamed: J6.7, J17.7
unnamed: J6.8, J17.8
VCC: C2.1, C3.1, C4.1, C6.1, C7.1, J1.1, J5.1, J5.4, J5.7, J5.10, J5.13, J5.16, J11.1, KCH1.2, KCH2.2, R1.1, R3.1, R4.1, R5.1, R6.1, R7.1, R8.1, R9.1, R10.1, R11.1, SAMCHAIN1.3, SAMCHAIN2.3, Ser1.7, Ser1.8, U1.55 (AREF), U2.2 (VO), U3.8 (VCC); also elsewhere on the board

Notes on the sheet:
PERIPHOUT - Output from peripheral to master (output here) MASTEROUT - Output from master to peripheral (input here) SYNC/LOAD- display to outputs on falling edge CLOCK - Change on rising edge, read on falling edge Pull up DRV to find if that SAM is connected
OUT IN
IN OUT
SAMPWR on 9/10 not used

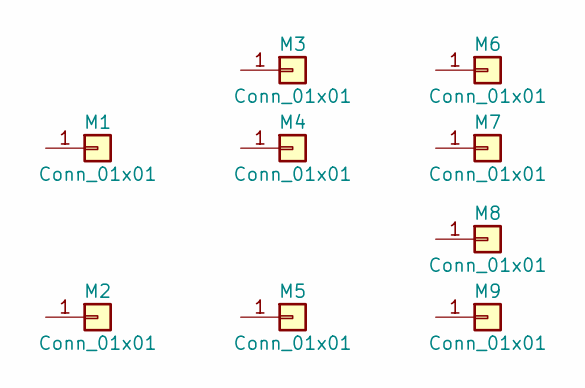
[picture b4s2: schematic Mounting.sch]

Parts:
M1, M2, M3, M4, M5, M6, M7, M8, M9: Conn_01x01; Mounting#4

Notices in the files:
Firmware/10to26IRQ_PIC16Indicators.X/mcc_generated_files/pin_manager.h:
(c) 2018 Microchip Technology Inc. and its subsidiaries.
